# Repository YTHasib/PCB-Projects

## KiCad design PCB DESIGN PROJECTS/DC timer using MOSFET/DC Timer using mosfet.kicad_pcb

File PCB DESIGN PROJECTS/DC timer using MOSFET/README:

# DC Timer Using MOSFET PCB

A simple DC delay timer circuit that activates a buzzer after a set time delay using an RC network and a MOSFET switch.

## Overview
This project demonstrates how passive components and a MOSFET can be used to create a time-delay switching circuit suitable for alarms, reminders, or delayed activation systems.

## Key Features
- RC-based timing control
- BS107 MOSFET used as a low-side switch
- Buzzer output for audible indication
- Battery-powered operation
- Minimal component count

## How It Works
The capacitor charges through a resistor. Once the MOSFET gate voltage exceeds its threshold, the MOSFET turns on and activates the buzzer after a delay.

## Files Included
- DC Timer using mosfet.kicad_sch – Schematic
- PCB layout file
- Schematic PDF
- 3D PCB render

## Tools Used
- KiCad 9
- Discrete analog components

## Skills Demonstrated
- MOSFET switching
- RC timing circuits
- Power electronics basics
- Compact PCB design

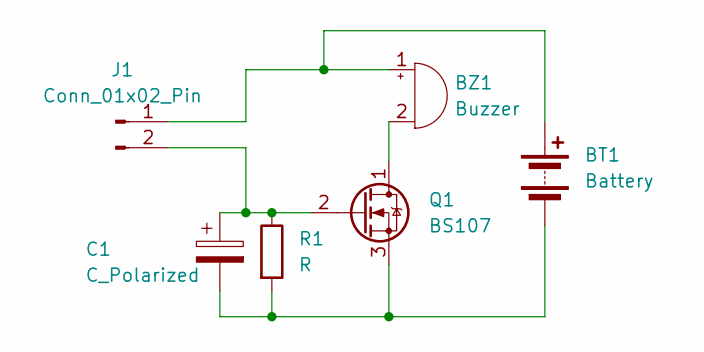
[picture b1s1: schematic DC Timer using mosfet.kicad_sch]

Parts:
BT1: Battery
BZ1: Buzzer
C1: C_Polarized
J1: Conn_01x02_Pin
Q1: BS107; TO-92_Inline
R1: R

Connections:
unnamed: BT1.1 (+), BZ1.1 (+), J1.1
unnamed: BT1.2 (-), C1.2, Q1.3 (S), R1.2
unnamed: BZ1.2 (-), Q1.1 (D)
unnamed: C1.1, J1.2, Q1.2 (G), R1.1

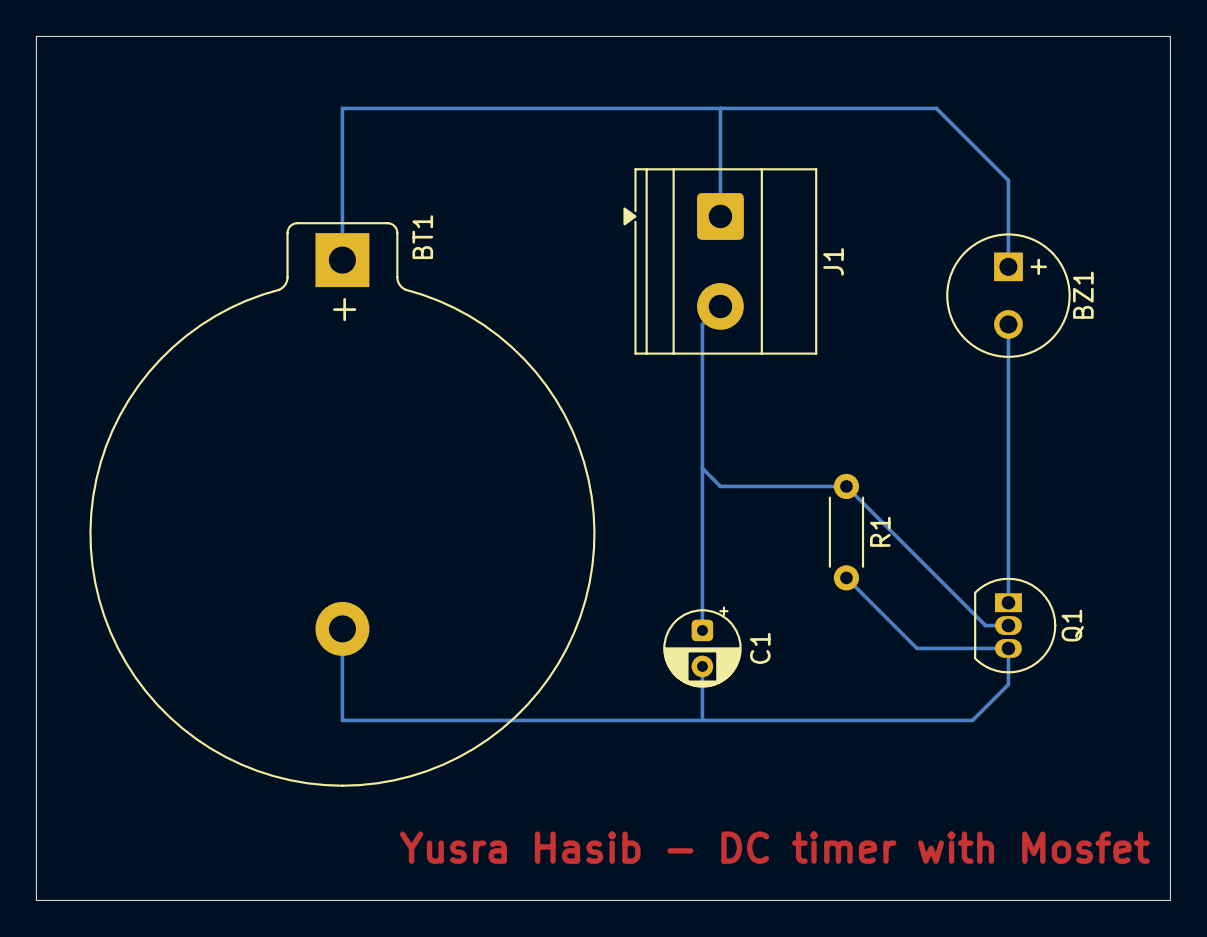
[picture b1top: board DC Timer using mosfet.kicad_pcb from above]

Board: 2 copper layers, 63.0 x 48.0 mm, 6 parts (0 on the bottom side), 4 nets.

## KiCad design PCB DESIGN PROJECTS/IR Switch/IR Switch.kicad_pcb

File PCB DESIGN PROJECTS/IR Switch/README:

# IR Switch PCB

An infrared-controlled switch that detects IR signals and generates a stable output using a TSOP IR receiver and a 555 timer.

## Overview
This PCB allows remote switching using an IR transmitter. The received signal is conditioned using a 555 timer to produce a reliable output signal and visual feedback.

## Key Features
- TSOP17xx infrared receiver
- NE555 timer for signal conditioning
- LED output indicator
- Operates on 5 V DC
- Screw terminal connections

## Design Highlights
- Clean separation of sensor and timing circuitry
- RC network for stable triggering
- Visual LED feedback for signal detection

## Files Included
- IR Switch.kicad_sch – Schematic
- PCB layout file
- Schematic PDF
- 3D PCB render

## Tools Used
- KiCad 9
- Mixed-signal PCB design

## Skills Demonstrated
- Infrared sensor integration
- 555 timer applications
- Signal conditioning
- Sensor-based PCB design

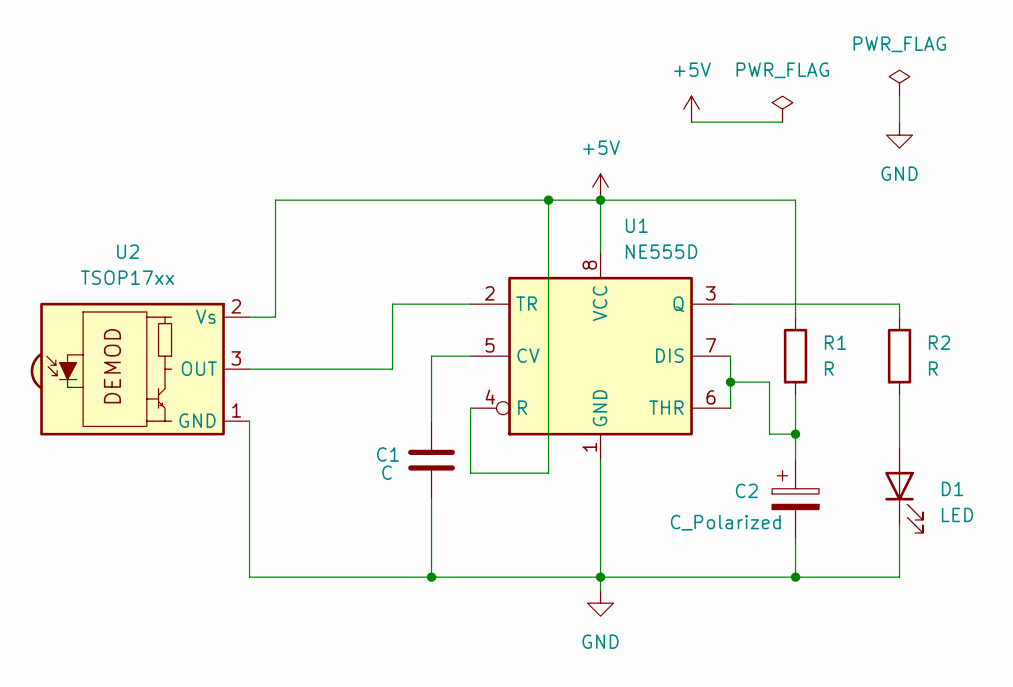
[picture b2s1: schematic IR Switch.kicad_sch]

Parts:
C1: C; C_Disc_D3.0mm_W1.6mm_P2.50mm
C2: C_Polarized; CP_Radial_D4.0mm_P2.00mm
D1: LED; LED_D3.0mm_IRGrey
R1, R2: R; R_Axial_DIN0204_L3.6mm_D1.6mm_P5.08mm_Horizontal
U1: NE555D; DIP-8_W7.62mm_LongPads
U2: TSOP17xx; Vishay_CAST-3Pin

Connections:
+5V: R1.1, U1.4 (R), U1.8 (VCC), U2.2 (Vs)
GND: C1.2, C2.2, D1.1 (K), U1.1 (GND), U2.1 (GND)
unnamed: D1.2 (A), R2.2
unnamed: C1.1, U1.5 (CV)
unnamed: C2.1, R1.2, U1.6 (THR), U1.7 (DIS)
unnamed: R2.1, U1.3 (Q)
unnamed: U1.2 (TR), U2.3 (OUT)

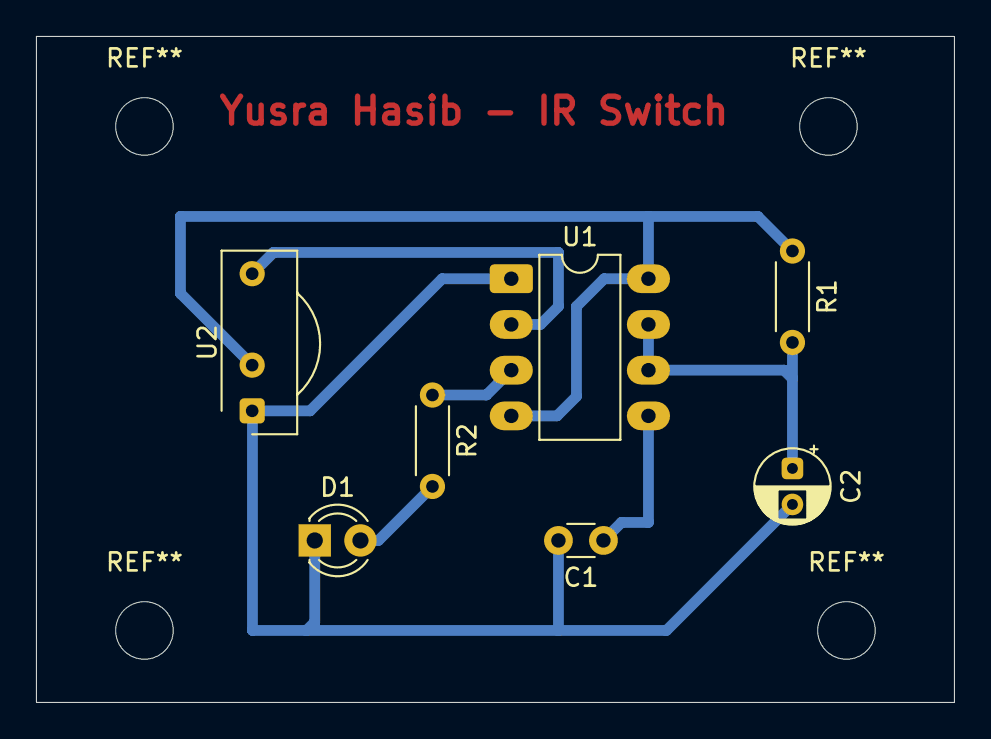
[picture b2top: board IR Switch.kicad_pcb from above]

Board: 2 copper layers, 51.0 x 37.0 mm, 7 parts (0 on the bottom side), 7 nets.

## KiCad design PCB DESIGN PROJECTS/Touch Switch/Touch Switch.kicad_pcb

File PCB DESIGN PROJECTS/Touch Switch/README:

# Touch Switch PCB

A capacitive touch-activated switch implemented using a 555 timer to toggle an output when a touch input is detected.

## Overview
This project demonstrates a simple human-interface circuit where touch input changes the capacitance at the trigger node, causing the circuit to activate an output indicator.

## Key Features
- Capacitive touch input pad
- NE555 timer-based control logic
- LED and buzzer output indicators
- Operates on 5 V DC
- Simple and intuitive user interaction

## How It Works
Touching the input pad alters the capacitance at the trigger pin of the 555 timer, changing its state and activating the output indicators.

## Files Included
- Touch Switch.kicad_sch – Schematic
- PCB layout file
- Schematic PDF
- 3D PCB render

## Tools Used
- KiCad 9
- Through-hole components

## Skills Demonstrated
- Capacitive sensing concepts
- Human-interface circuit design
- Timing and trigger circuits
- PCB layout and visualization

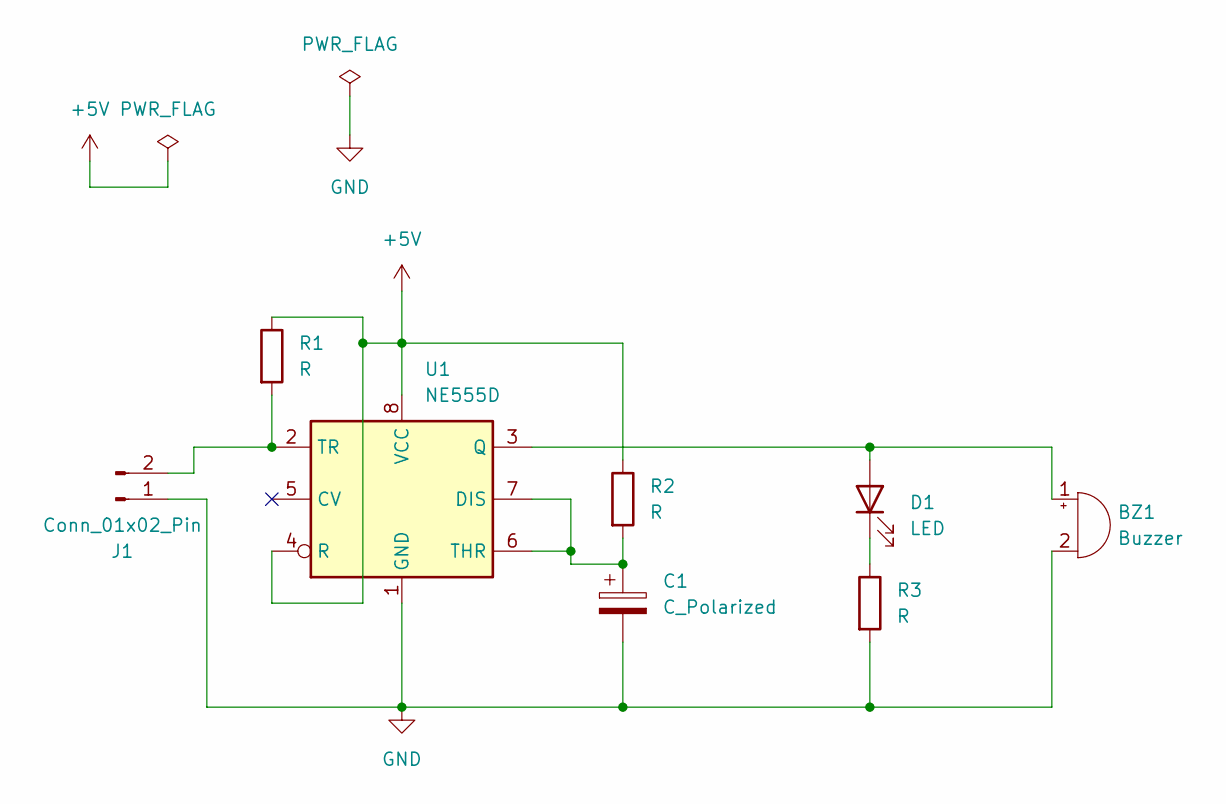
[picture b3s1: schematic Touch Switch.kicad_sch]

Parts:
BZ1: Buzzer; Buzzer_12x9.5RM7.6
C1: C_Polarized; CP_Radial_D5.0mm_P2.50mm
D1: LED; LED_D3.0mm_FlatTop
J1: Conn_01x02_Pin; TerminalBlock_Phoenix_MKDS-1-2-3.81_1x02_P3.81mm_Horizontal
R1: R; R_Axial_DIN0204_L3.6mm_D1.6mm_P7.62mm_Horizontal
R2, R3: R; R_Axial_DIN0207_L6.3mm_D2.5mm_P7.62mm_Horizontal
U1: NE555D; DIP-8_W7.62mm_LongPads

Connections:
+5V: R1.1, R2.1, U1.4 (R), U1.8 (VCC)
GND: BZ1.2 (-), C1.2, J1.1, R3.2, U1.1 (GND)
unnamed: BZ1.1 (+), D1.2 (A), U1.3 (Q)
unnamed: D1.1 (K), R3.1
unnamed: J1.2, R1.2, U1.2 (TR)
unnamed: C1.1, R2.2, U1.6 (THR), U1.7 (DIS)

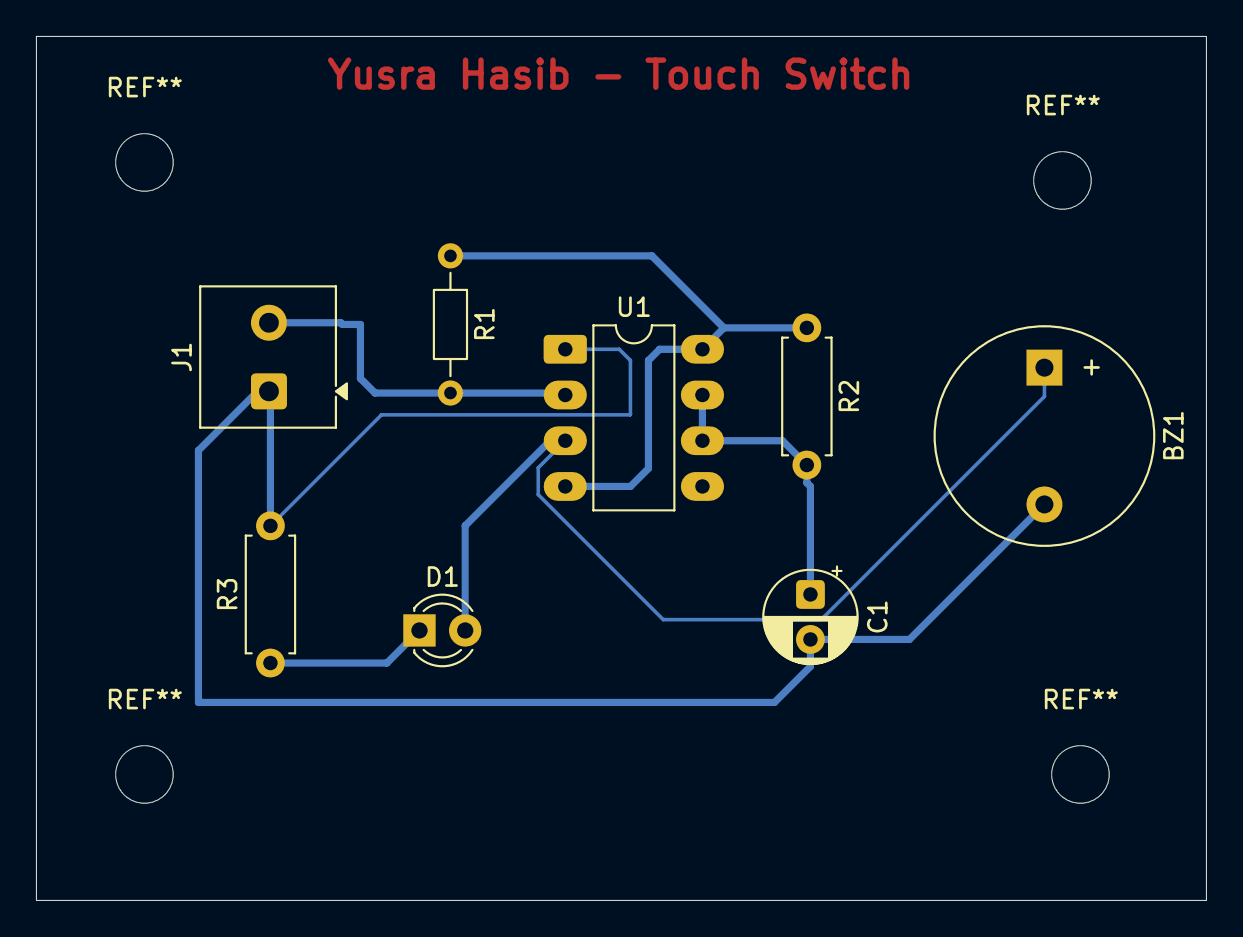
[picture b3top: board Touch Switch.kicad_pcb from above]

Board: 2 copper layers, 65.0 x 48.0 mm, 8 parts (0 on the bottom side), 6 nets.

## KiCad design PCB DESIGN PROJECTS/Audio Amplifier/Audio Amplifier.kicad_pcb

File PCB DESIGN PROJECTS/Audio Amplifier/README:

# Audio Amplifier PCB

A low-power audio amplifier PCB designed using the LM386 audio amplifier IC.  
This board amplifies a low-level audio signal to drive a small speaker or external audio load.

## Overview
The design focuses on simplicity, clean signal routing, and ease of assembly using through-hole components. It includes adjustable gain and proper input/output coupling to ensure stable audio performance.

## Key Features
- LM386-based audio amplifier
- Adjustable gain using a potentiometer
- AC-coupled input and output
- Operates on a 12 V DC supply
- Screw terminals for audio input and output

## Design Highlights
- Input coupling capacitor to block DC offsets
- External gain control network
- Output decoupling for load protection
- Compact single-layer PCB layout

## Files Included
- Audio Amplifier.kicad_sch – Schematic
- Audio Amplifier.kicad_pcb – PCB layout
- schematic.pdf – Exported schematic
- pcb_3d.png – 3D PCB render

## Tools Used
- KiCad 9
- Through-hole components

## Skills Demonstrated
- Analog circuit design
- Audio signal amplification
- PCB schematic capture and layout
- Design documentation and visualization

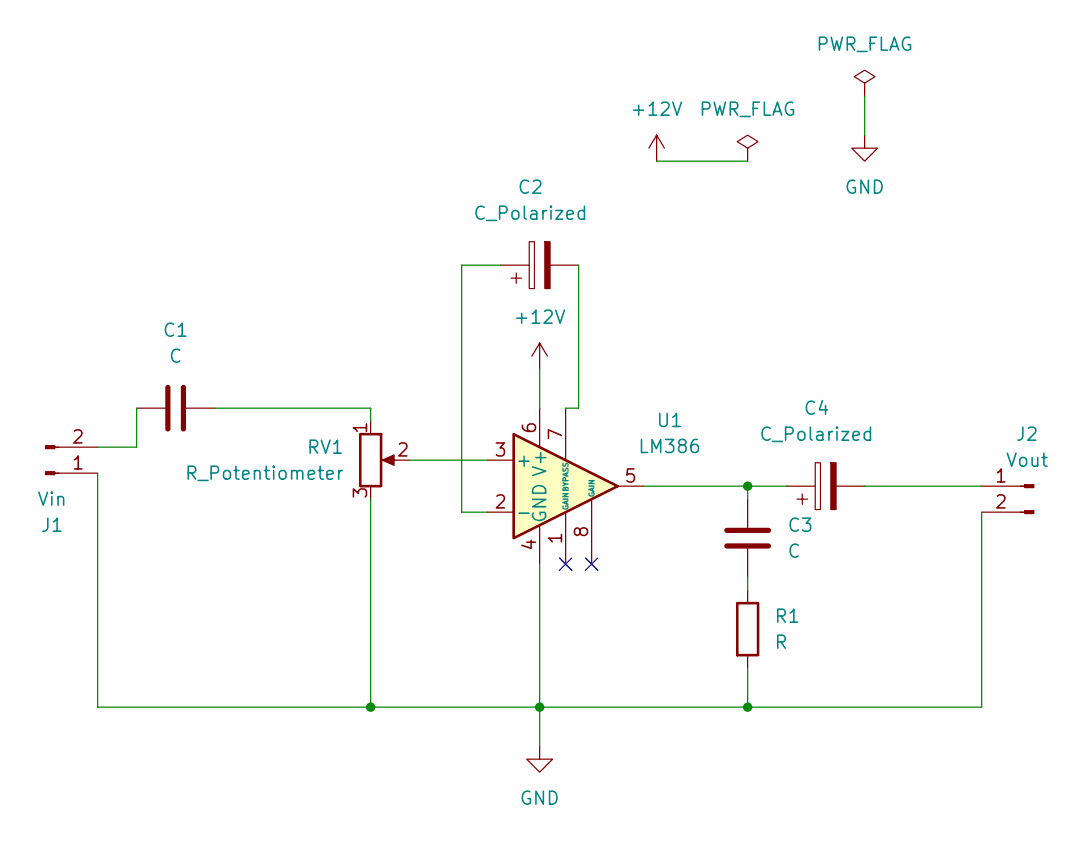
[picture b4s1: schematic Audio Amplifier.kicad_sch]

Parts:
C1, C3: C; C_Disc_D4.3mm_W1.9mm_P5.00mm
C2, C4: C_Polarized; C_Radial_D5.0mm_H5.0mm_P2.00mm
J1: Vin; TerminalBlock_Phoenix_MKDS-1,5-2-5.08_1x02_P5.08mm_Horizont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
J2: Vout; TerminalBlock_Phoenix_MKDS-1,5-2-5.08_1x02_P5.08mm_Horizont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
R1: R; R_Axial_DIN0204_L3.6mm_D1.6mm_P7.62mm_Horizontal
RV1: R_Potentiometer; Potentiometer_Runtron_RM-065_Vertical
U1: LM386; DIP-10_W7.62mm_LongPads

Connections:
+12V: U1.6 (V+)
GND: J1.1, J2.2, R1.2, RV1.3, U1.4 (GND)
unnamed: C1.2, RV1.1
unnamed: C3.1, C4.1, U1.5
unnamed: C3.2, R1.1
unnamed: C1.1, J1.2
unnamed: C4.2, J2.1
unnamed: RV1.2, U1.3 (+)
unnamed: C2.1, U1.2 (-)
unnamed: C2.2, U1.7 (BYPASS)

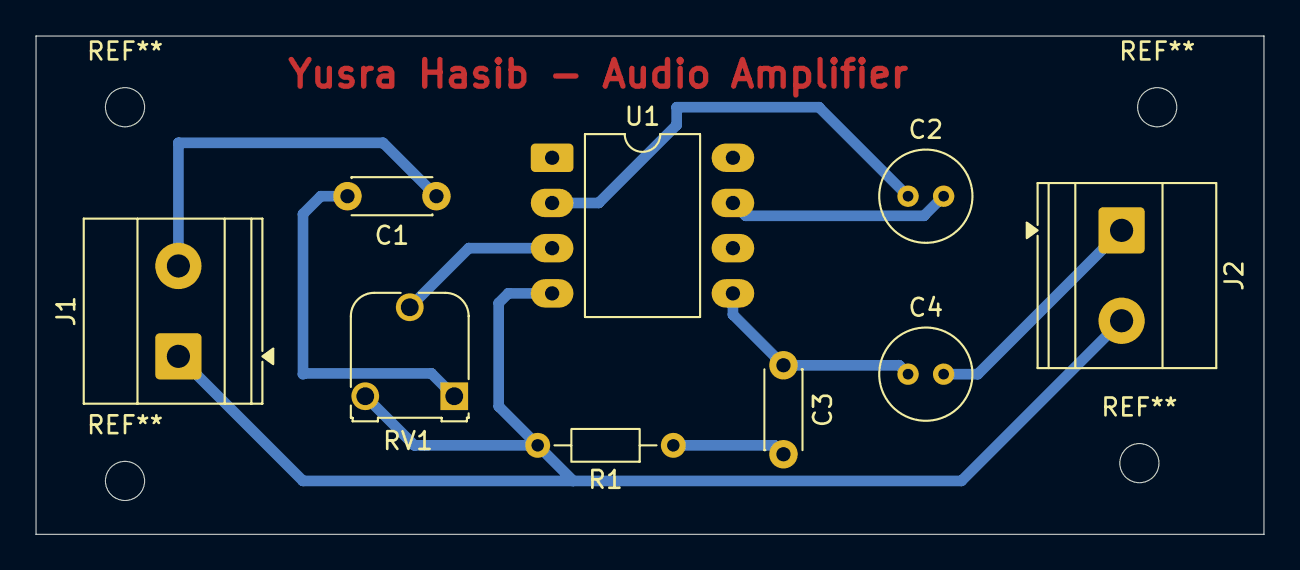
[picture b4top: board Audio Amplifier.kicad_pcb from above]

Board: 2 copper layers, 69.0 x 28.0 mm, 9 parts (0 on the bottom side), 9 nets.

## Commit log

2026-01-10 Add README for Audio Amplifier PCB project
    Added README for Audio Amplifier PCB project detailing features, design highlights, and included files.
2026-01-10 Create README for DC Timer Using MOSFET project
    Added README for DC Timer project detailing features, operation, and included files.
2026-01-10 Add README for IR Switch PCB project
    Added a README file for the IR Switch PCB project, detailing its features, design highlights, included files, tools used, and skills demonstrated.
2026-01-10 Add README for Touch Switch PCB project
    Added README for Touch Switch PCB project detailing features, functionality, and tools used.
